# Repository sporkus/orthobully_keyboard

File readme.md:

Ortholinear PCB for bully keyboard
------------------------------

This is a "split" Ortholinear pcb made for [Bully keyboard](https://mkh.works/#bully).

### Features
- 5 columns on each side, with a 3 column center cluster
- RP2040

### Supported layouts

### Production files
JLCPCB [production files](pcb/production) are provided. Components placement should be correct, but as always, do your own diligence when odering.

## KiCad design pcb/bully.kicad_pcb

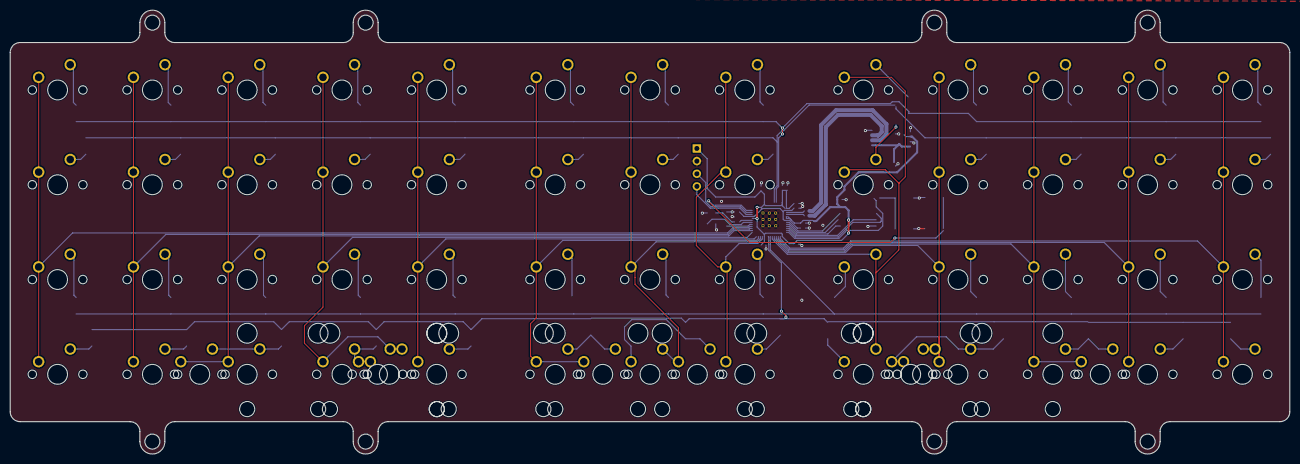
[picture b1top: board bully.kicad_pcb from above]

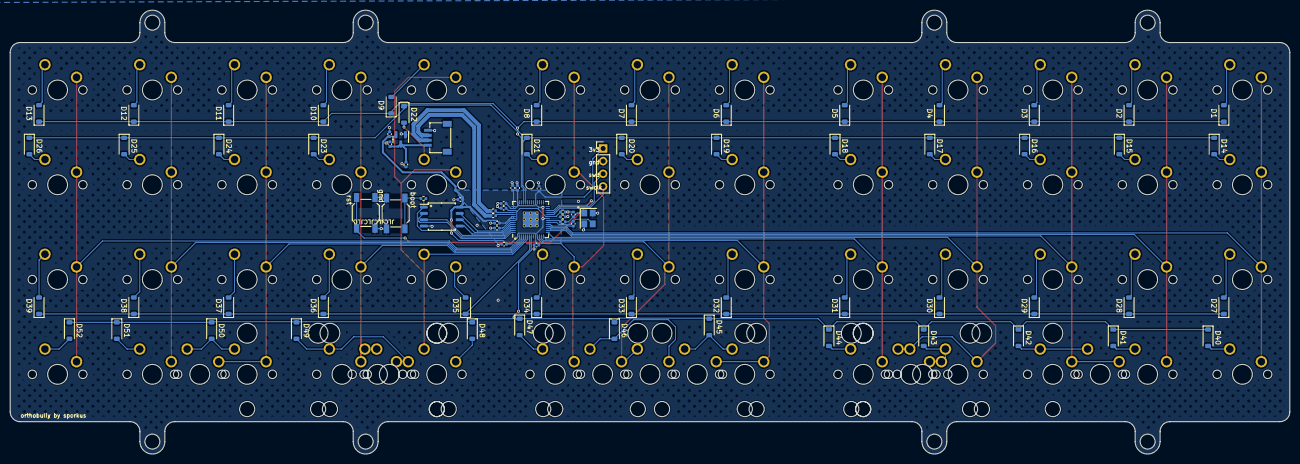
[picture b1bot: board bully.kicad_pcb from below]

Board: 2 copper layers, 257.2 x 89.2 mm, 141 parts (81 on the bottom side), 90 nets.

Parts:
C1, C5, C6, C9, C10, C11, C12, C13, C14, C15: 100nF; C_0402_1005Metric
C2, C3: 22pF; C_0402_1005Metric
C4, C7, C16, C17: 1uF; C_0402_1005Metric
C8: 10uF; C_0402_1005Metric
D1, D2, D3, D4, D5, D6, D7, D8, D9, D10, D11, D12, D13, D14, D15, D16, D17, D18, D19, D20, D21, D22, D23, D24, D25, D26, D27, D28, D29, D30, D31, D32, D33, D34, D35, D36, D37, D38, D39, D40, D41, D42, D43, D44, D45, D46, D47, D48, D49, D50, D51, D52: 1N4148W; D_SOD-123
J1: SM04B-SRSS-TB(LF)(SN); JST-SR-4
J2: Conn_01x04; PinHeader_1x04_P2.54mm_Vertical
R1, R7: 1k; R_0402_1005Metric
R5, R6: 27R; R_0402_1005Metric
SW1, SW2, SW3, SW4, SW5, SW6, SW7, SW8, SW9, SW10, SW11, SW12, SW13, SW14, SW15, SW16, SW17, SW18, SW19, SW20, SW21, SW22, SW23, SW24, SW25, SW26, SW27, SW28, SW29, SW30, SW31, SW32, SW33, SW34, SW35, SW36, SW37, SW38, SW39, SW40, SW41, SW42, SW44, SW45, SW47, SW48, SW50, SW51, SW52: SW_Push; MX-Solderable-1U
SW43, SW46, SW49: SW_Push; MX-Solderable-3U-ReversedStabilizers
SW53, SW54, SW55, SW56: SW_Push; MX-Solderable-2U-ReversedStabilizers
SW57, SW60: SW_Push; MX-Solderable-1.5U
SW58, SW59: SW_Push; MX-Solderable-2.25U-ReversedStabilizers
SW_BOOT1: SKQGABE010; SW_SPST_SKQG_WithoutStem
SW_RST1: SKQGABE010; SW_SPST_SKQG_WithoutStem
U1: W25Q128JVS; SOIC-8_5.23x5.23mm_P1.27mm
U3: RP2040; RP2040-QFN-56
U4: XC6206PxxxMR-Regulator_Linear; SOT-23
Y1: 12MHz; Crystal_SMD_3225-4Pin_3.2x2.5mm

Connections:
+1V1: C4.1, C5.1, C6.1, U3.23 (DVDD), U3.45 (VREG_VOUT), U3.50 (DVDD)
+3V3: C1.1, C7.1, C9.1, C10.1, C11.1, C12.1, C13.1, C14.1, C15.1, C17.2, J2.1, U1.8 (VCC), U3.1 (IOVDD), U3.10 (IOVDD), U3.22 (IOVDD), U3.33 (IOVDD), U3.42 (IOVDD), U3.43 (ADC_AVDD), U3.44 (VREG_VIN), U3.48 (USB_VDD), U3.49 (IOVDD), U4.2 (VO)
+5V: C8.1, C16.2, J1.1, U4.3 (VI)
/D_+: R5.2, U3.47 (D+)
/D_-: R6.2, U3.46 (D-)
/XTAL_O: C3.2, R7.1, Y1.1
/~USB_BOOT: R1.1, SW_BOOT1.2
COL1: SW1.1, SW14.1, SW27.1, SW40.1, U3.18 (GPIO15)
COL2: SW2.1, SW15.1, SW28.1, SW41.1, U3.17 (GPIO14)
COL3: SW3.1, SW16.1, SW29.1, SW42.1, SW57.1, U3.16 (GPIO13)
COL4: SW4.1, SW17.1, SW30.1, SW43.1, SW53.2, SW58.2, U3.15 (GPIO12)
COL5: SW5.1, SW18.1, SW31.1, SW44.1, U3.14 (GPIO11)
COL6: SW6.1, SW19.1, SW32.1, SW45.1, SW54.1, U3.13 (GPIO10)
COL7: SW7.1, SW20.1, SW33.1, SW46.2, SW55.1, U3.12 (GPIO9)
COL8: SW8.1, SW21.1, SW34.1, SW47.1, U3.11 (GPIO8)
COL9: SW9.1, SW22.1, SW35.2, SW48.2, U3.6 (GPIO4)
COL10: SW10.1, SW23.1, SW36.1, SW49.1, SW56.2, SW59.2, U3.5 (GPIO3)
COL11: SW11.1, SW24.1, SW37.1, SW50.1, SW60.1, U3.4 (GPIO2)
COL12: SW12.1, SW25.1, SW38.1, SW51.1, U3.3 (GPIO1)
COL13: SW13.1, SW26.1, SW39.1, SW52.1, U3.2 (GPIO0)
D_N: J1.2, R6.1
D_P: J1.3, R5.1
GND: C1.2, C2.1, C3.1, C4.2, C5.2, C6.2, C7.2, C8.2, C9.2, C10.2, C11.2, C12.2, C13.2, C14.2, C15.2, C16.1, C17.1, J1.4, J2.2, SW_BOOT1.1, SW_RST1.1, U1.4 (GND), U3.19 (TESTEN), U3.57 (GND), U4.1 (GND), Y1.2, Y1.4
unnamed: D1.2 (A), SW1.2
unnamed: D2.2 (A), SW2.2
unnamed: D3.2 (A), SW3.2
unnamed: D4.2 (A), SW4.2
unnamed: D5.2 (A), SW5.2
unnamed: D6.2 (A), SW6.2
unnamed: D7.2 (A), SW7.2
unnamed: D8.2 (A), SW8.2
unnamed: D9.2 (A), SW9.2
unnamed: D10.2 (A), SW10.2
unnamed: D11.2 (A), SW11.2
unnamed: D12.2 (A), SW12.2
unnamed: D13.2 (A), SW13.2
unnamed: D14.2 (A), SW14.2
unnamed: D15.2 (A), SW15.2
unnamed: D16.2 (A), SW16.2
unnamed: D17.2 (A), SW17.2
unnamed: D18.2 (A), SW18.2
unnamed: D19.2 (A), SW19.2
unnamed: D20.2 (A), SW20.2
unnamed: D21.2 (A), SW21.2
unnamed: D22.2 (A), SW22.2
unnamed: D23.2 (A), SW23.2
unnamed: D24.2 (A), SW24.2
unnamed: D25.2 (A), SW25.2
unnamed: D26.2 (A), SW26.2
unnamed: D27.2 (A), SW27.2
unnamed: D28.2 (A), SW28.2
unnamed: D29.2 (A), SW29.2
unnamed: D30.2 (A), SW30.2
unnamed: D31.2 (A), SW31.2
unnamed: D32.2 (A), SW32.2
unnamed: D33.2 (A), SW33.2
unnamed: D34.2 (A), SW34.2
unnamed: D35.2 (A), SW35.1
unnamed: D36.2 (A), SW36.2
unnamed: D37.2 (A), SW37.2
unnamed: D38.2 (A), SW38.2
unnamed: D39.2 (A), SW39.2
unnamed: D40.2 (A), SW40.2
unnamed: D41.2 (A), SW41.2
unnamed: D42.2 (A), SW42.2, SW57.2
unnamed: D43.2 (A), SW43.2, SW53.1, SW58.1
unnamed: D44.2 (A), SW44.2
unnamed: D45.2 (A), SW45.2, SW54.2
unnamed: D46.2 (A), SW46.1, SW55.2
unnamed: D47.2 (A), SW47.2
unnamed: D48.2 (A), SW48.1
unnamed: D49.2 (A), SW49.2, SW56.1, SW59.1
unnamed: D50.2 (A), SW50.2, SW60.2
unnamed: D51.2 (A), SW51.2
unnamed: D52.2 (A), SW52.2
QSPI_CLK: U1.6 (CLK), U3.52 (QSPI_SCLK)
QSPI_SS: R1.2, U1.1 (~CS), U3.56 (QSPI_SS_N)
ROW1: D1.1 (K), D2.1 (K), D3.1 (K), D4.1 (K), D5.1 (K), D6.1 (K), D7.1 (K), D8.1 (K), D9.1 (K), D10.1 (K), D11.1 (K), D12.1 (K), D13.1 (K), U3.39 (GPIO27/ADC1)
ROW2: D14.1 (K), D15.1 (K), D16.1 (K), D17.1 (K), D18.1 (K), D19.1 (K), D20.1 (K), D21.1 (K), D22.1 (K), D23.1 (K), D24.1 (K), D25.1 (K), D26.1 (K), U3.38 (GPIO26/ADC0)
ROW3: D27.1 (K), D28.1 (K), D29.1 (K), D30.1 (K), D31.1 (K), D32.1 (K), D33.1 (K), D34.1 (K), D35.1 (K), D36.1 (K), D37.1 (K), D38.1 (K), D39.1 (K), U3.7 (GPIO5)
ROW4: D40.1 (K), D41.1 (K), D42.1 (K), D43.1 (K), D44.1 (K), D45.1 (K), D46.1 (K), D47.1 (K), D48.1 (K), D49.1 (K), D50.1 (K), D51.1 (K), D52.1 (K), U3.8 (GPIO6)
SD0: U1.5 (DI(IO0)), U3.53 (QSPI_SD0)
SD1: U1.2 (DO(IO1)), U3.55 (QSPI_SD1)
SD2: U1.3 (IO2), U3.54 (QSPI_SD2)
SD3: U1.7 (IO3), U3.51 (QSPI_SD3)
SWCLK: J2.4, U3.24 (SWCLK)
SWD: J2.3, U3.25 (SWDIO)
XTAL_IN: C2.2, U3.20 (XTAL_IN), Y1.3
XTAL_OUT: R7.2, U3.21 (XTAL_OUT)
~RESET: SW_RST1.2, U3.26 (~RUN)

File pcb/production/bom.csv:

Designator,Footprint,Quantity,Value,LCSC Part #
"C1, C10, C11, C12, C13, C14, C15, C5, C6, C9",402,10,100nF,C1525
"C16, C17, C4, C7",402,4,1uF,C52923
"C2, C3",402,2,22pF,C1555
C8,402,1,10uF,C15525 
"D1, D10, D11, D12, D13, D14, D15, D16, D17, D18, D19, D2, D20, D21, D22, D23, D24, D25, D26, D27, D28, D29, D3, D30, D31, D32, D33, D34, D35, D36, D37, D38, D39, D4, D40, D41, D42, D43, D44, D45, D46, D47, D48, D49, D5, D50, D51, D52, D6, D7, D8, D9",D_SOD-123,52,1N4148W,C81598
J1,JST-SR-4,1,SM04B-SRSS-TB(LF)(SN),C3029343 
"R1, R7",402,2,1k,C11702
"R5, R6",402,2,27R,C25092
U1,SOIC-8_5.23x5.23mm_P1.27mm,1,W25Q128JVS,C97521
U3,RP2040-QFN-56,1,RP2040,C2040
U4,SOT-23,1,XC6206PxxxMR-Regulator_Linear,C5446
Y1,Crystal_SMD_3225-4Pin_3.2x2.5mm,1,12MHz,C9002
SW_BOOT1,TL3342,1,SKQG,C318884
SW_RST1,TL3342,1,SKQG,C318884

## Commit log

2023-06-07 looks good for ordering but entirely untested
2023-06-07 adding KLE json
2023-06-16 updated bom
2024-01-29 Added JLC part numbers, remove unused parts from BOM and position files
2024-02-06 Added 150/225 bottom row for hhkb support
    Fixed positions of many bottom row alternate layouts. No BOM changes, just moved one diode and a few conflicting traces.
    Gerbers have been updated
2024-02-06 Add new layouts picture
